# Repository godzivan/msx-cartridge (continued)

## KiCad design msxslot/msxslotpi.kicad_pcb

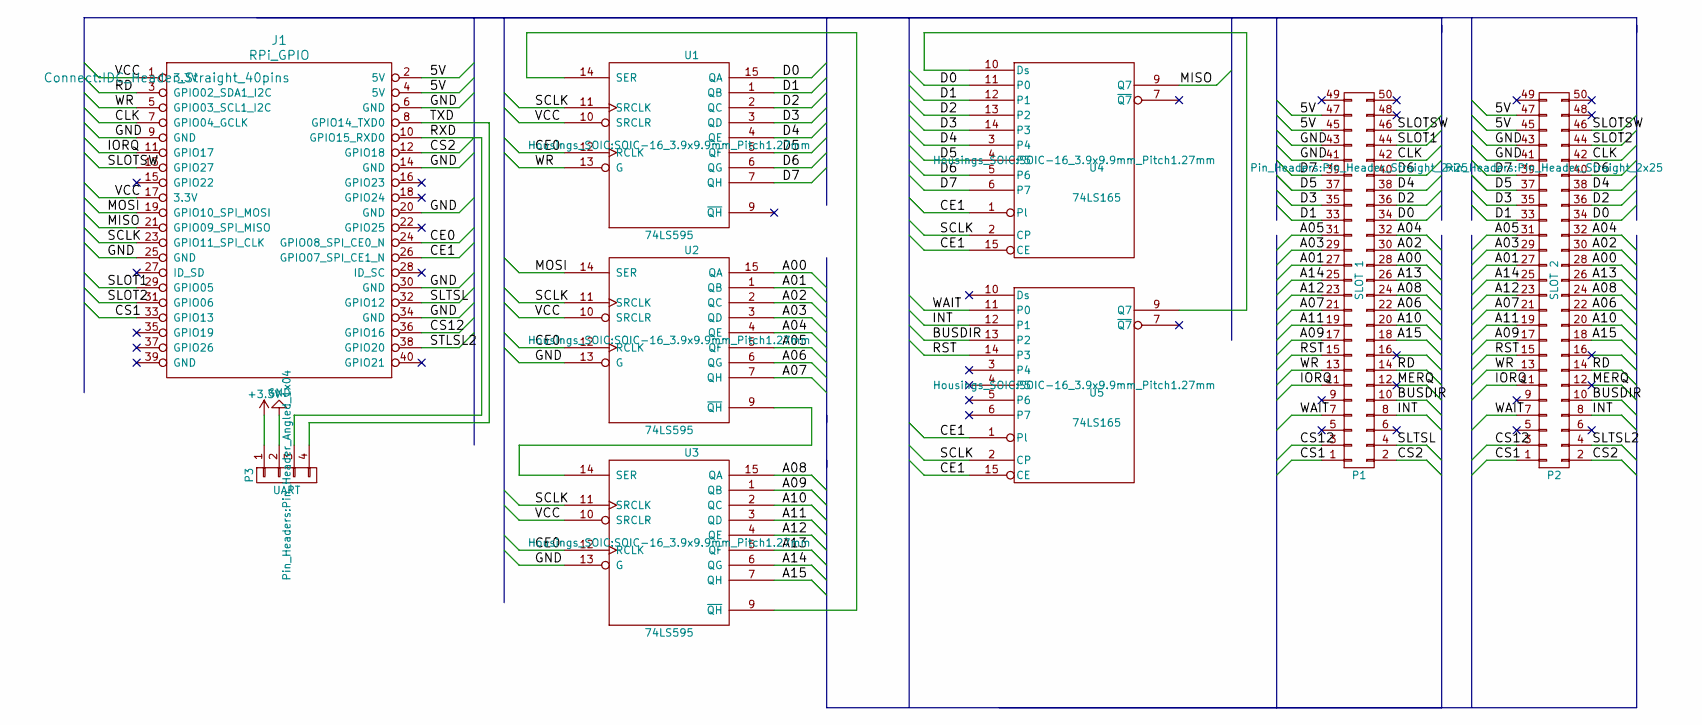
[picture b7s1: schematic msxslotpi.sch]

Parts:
J1: RPi_GPIO; IDC_Header_Straight_40pins
P1: SLOT 1; Pin_Header_Straight_2x25
P2: SLOT 2; Pin_Header_Straight_2x25
P3: UART; Pin_Header_Angled_1x04
U1, U2, U3: 74LS595; SOIC-16_3.9x9.9mm_Pitch1.27mm
U4, U5: 74LS165; SOIC-16_3.9x9.9mm_Pitch1.27mm

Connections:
+3V3: P3.1
/5V: J1.2 (5V), J1.4 (5V), P1.45, P1.47, P2.45, P2.47
/A00: P1.28, P2.28, U2.15 (QA)
/A01: P1.27, P2.27, U2.1 (QB)
/A02: P1.30, P2.30, U2.2 (QC)
/A03: P1.29, P2.29, U2.3 (QD)
/A04: P1.32, P2.32, U2.4 (QE)
/A05: P1.31, P2.31, U2.5 (QF)
/A06: P1.22, P2.22, U2.6 (QG)
/A07: P1.21, P2.21, U2.7 (QH)
/A08: P1.24, P2.24, U3.15 (QA)
/A09: P1.17, P2.17, U3.1 (QB)
/A10: P1.20, P2.20, U3.2 (QC)
/A11: P1.19, P2.19, U3.3 (QD)
/A12: P1.23, P2.23, U3.4 (QE)
/A13: P1.26, P2.26, U3.5 (QF)
/A14: P1.25, P2.25, U3.6 (QG)
/A15: P1.18, P2.18, U3.7 (QH)
/BUSDIR: P1.10, P2.10, U5.13 (P2)
/CE0: J1.24 (GPIO08_SPI_CE0_N), U1.12 (RCLK), U2.12 (RCLK), U3.12 (RCLK)
/CE1: J1.26 (GPIO07_SPI_CE1_N), U4.1 (Pl), U4.15 (CE), U5.1 (Pl), U5.15 (CE)
/CLK: J1.7 (GPIO04_GCLK), P1.42, P2.42
/CS1: J1.33 (GPIO13), P1.1, P2.1
/CS2: J1.12 (GPIO18), P1.2, P2.2
/CS12: J1.36 (GPIO16), P1.3, P2.3
/D0: P1.34, P2.34, U1.15 (QA), U4.11 (P0)
/D1: P1.33, P2.33, U1.1 (QB), U4.12 (P1)
/D2: P1.36, P2.36, U1.2 (QC), U4.13 (P2)
/D3: P1.35, P2.35, U1.3 (QD), U4.14 (P3)
/D4: P1.38, P2.38, U1.4 (QE), U4.3 (P4)
/D5: P1.37, P2.37, U1.5 (QF), U4.4 (P5)
/D6: P1.40, P2.40, U1.6 (QG), U4.5 (P6)
/D7: P1.39, P2.39, U1.7 (QH), U4.6 (P7)
/INT: P1.8, P2.8, U5.12 (P1)
/IORQ: J1.11 (GPIO17), P1.11, P2.11
/MERQ: P1.12, P2.12
/MISO: J1.21 (GPIO09_SPI_MISO), U4.9 (Q7)
/MOSI: J1.19 (GPIO10_SPI_MOSI), U2.14 (SER)
/RD: J1.3 (GPIO02_SDA1_I2C), P1.14, P2.14
/RST: P1.15, P2.15, U5.14 (P3)
/RXD: J1.10 (GPIO15_RXD0), P3.3
/SCLK: J1.23 (GPIO11_SPI_CLK), U1.11 (SRCLK), U2.11 (SRCLK), U3.11 (SRCLK), U4.2 (CP), U5.2 (CP)
/SLOT1: J1.29 (GPIO05), P1.44
/SLOT2: J1.31 (GPIO06), P2.44
/SLOTSW: J1.13 (GPIO27), P1.46, P2.46
/SLTSL: J1.32 (GPIO12), P1.4
/SLTSL2: P2.4
/STLSL2: J1.38 (GPIO20)
/TXD: J1.8 (GPIO14_TXD0), P3.4
/WAIT: P1.7, P2.7, U5.11 (P0)
/WR: J1.5 (GPIO03_SCL1_I2C), P1.13, P2.13, U1.13 (G)
GND: J1.6 (GND), J1.9 (GND), J1.14 (GND), J1.20 (GND), J1.25 (GND), J1.30 (GND), J1.34 (GND), P1.41, P1.43, P2.41, P2.43, P3.2, U1.8 (GND), U2.8 (GND), U2.13 (G), U3.8 (GND), U3.13 (G), U4.8 (GND), U5.8 (GND)
unnamed: U1.14 (SER), U3.9 (~QH)
unnamed: U2.9 (~QH), U3.14 (SER)
unnamed: U4.10 (Ds), U5.9 (Q7)
VCC: J1.1 (3.3V), J1.17 (3.3V), U1.10 (SRCLR), U1.16 (VCC), U2.10 (SRCLR), U2.16 (VCC), U3.10 (SRCLR), U3.16 (VCC), U4.16 (VCC), U5.16 (VCC)

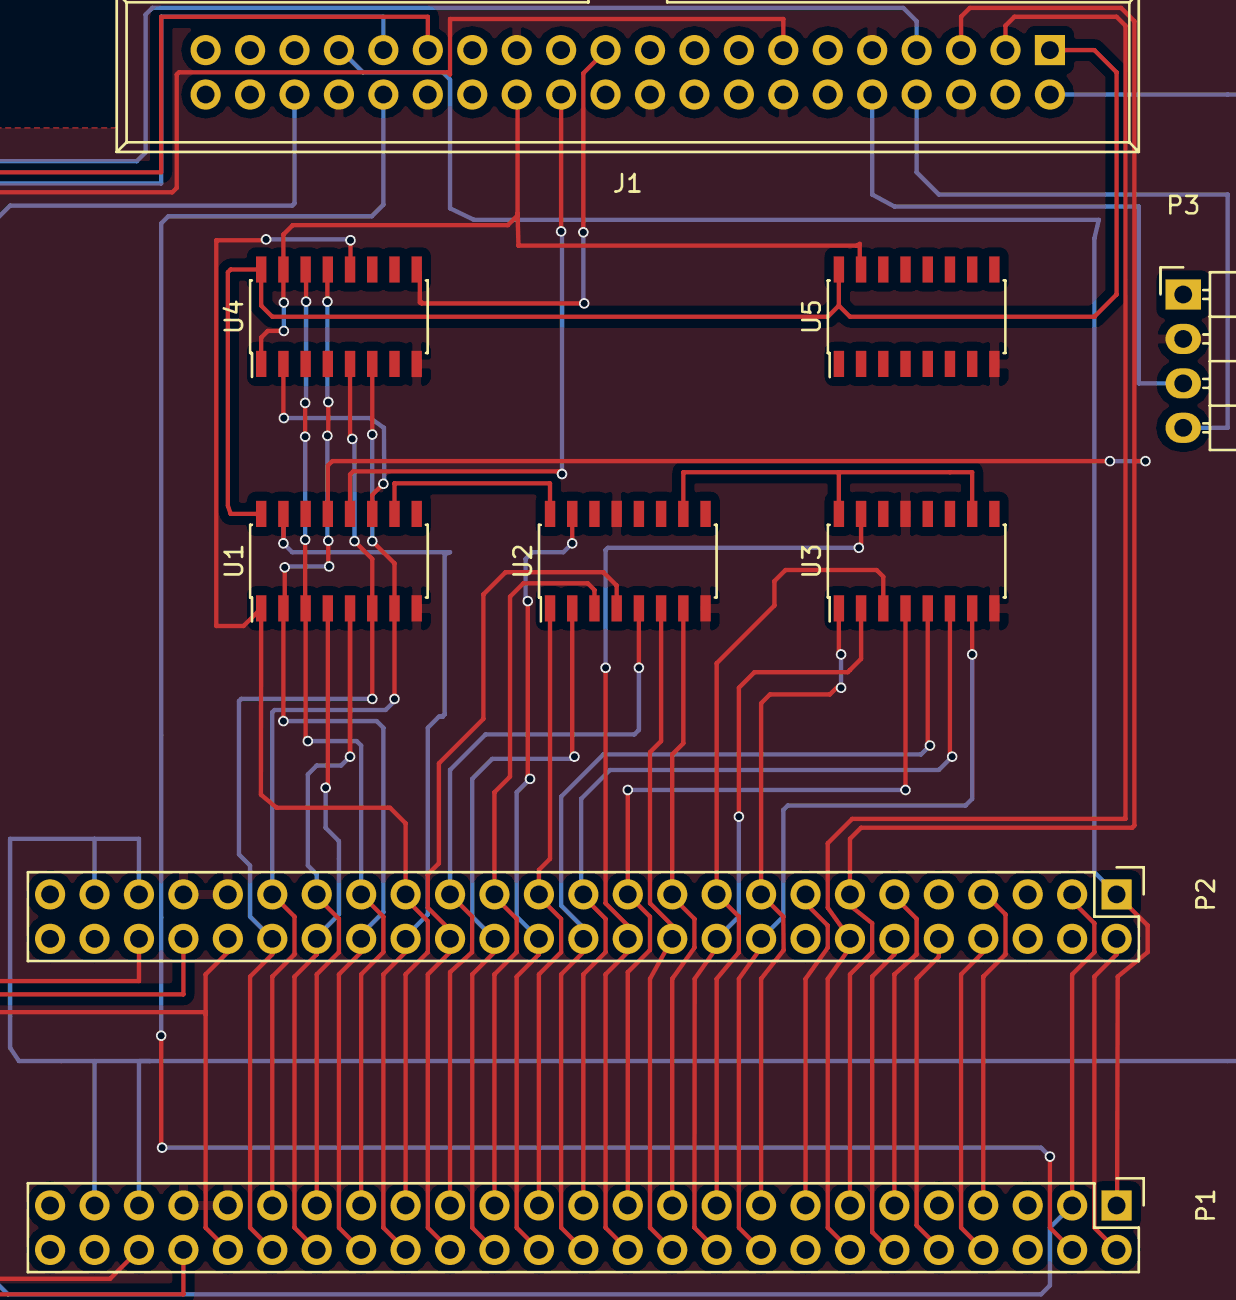
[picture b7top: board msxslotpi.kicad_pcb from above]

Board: 2 copper layers, 9 parts (0 on the bottom side), 53 nets.
